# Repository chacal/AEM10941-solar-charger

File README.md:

# AEM10941 Solar Charger

KiCad hardware files for a simple [e-peas AEM10941](https://e-peas.com/product/aem10941/) based solar charger PCB.

## Schematics

* [PDF](AEM10941%20Solar%20Charger.pdf)

## Board rendering

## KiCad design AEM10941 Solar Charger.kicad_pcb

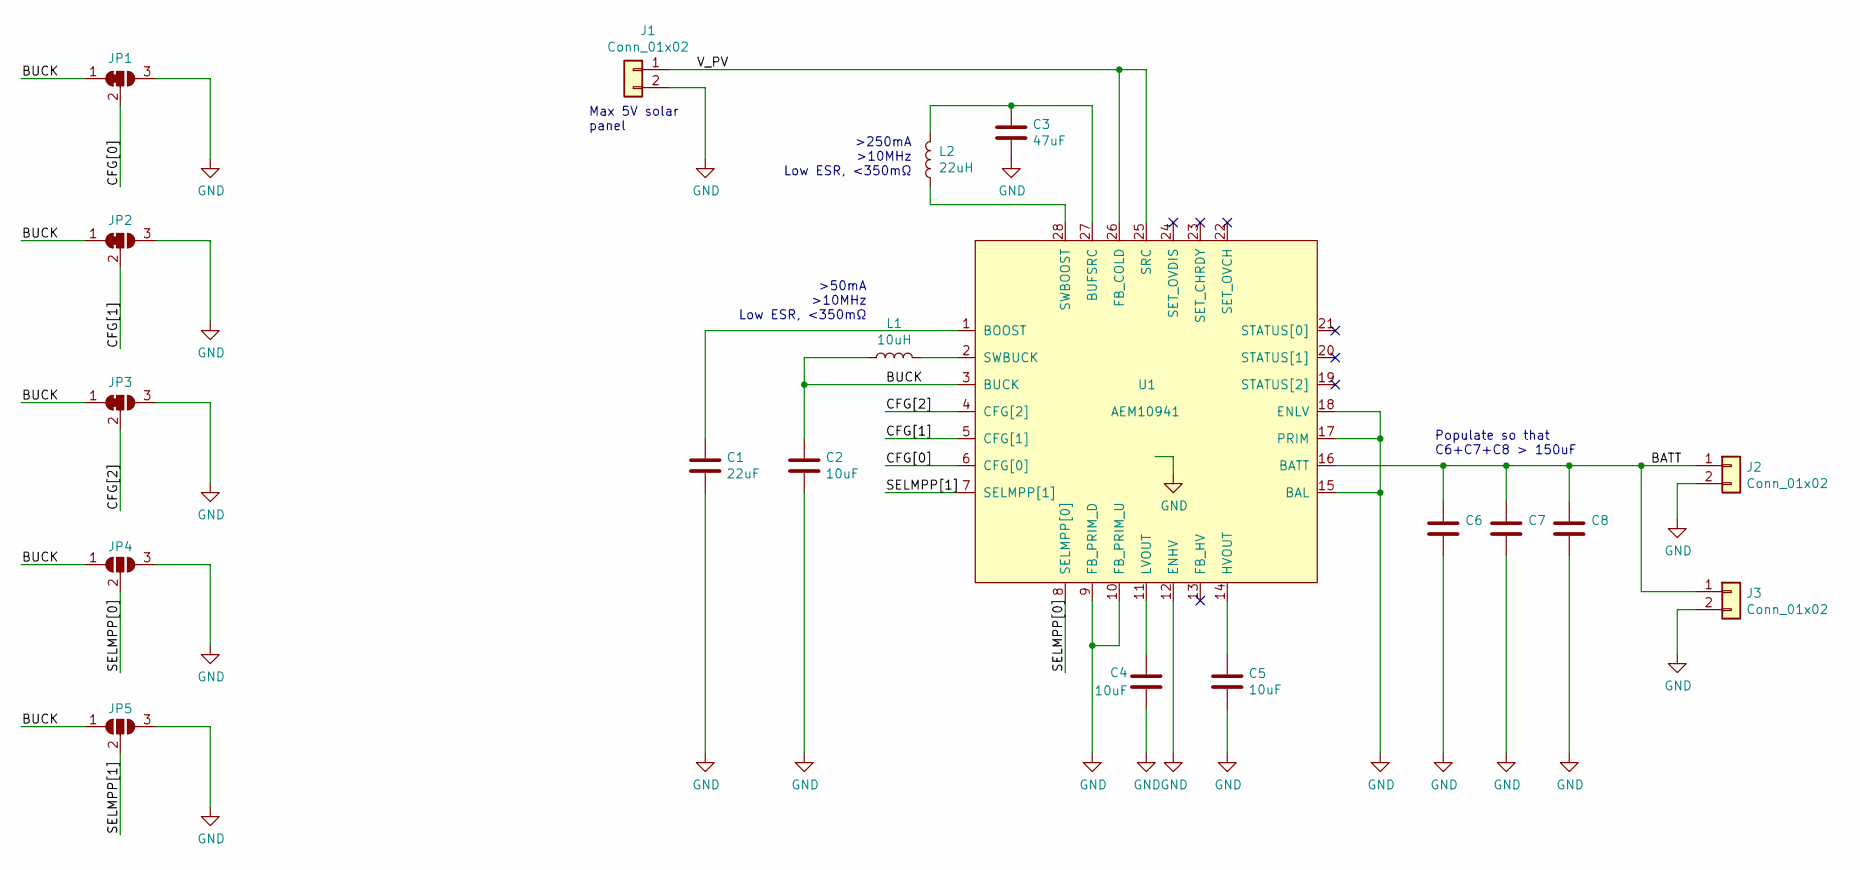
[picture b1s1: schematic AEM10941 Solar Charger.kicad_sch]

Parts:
C1: 22uF; C_0805_2012Metric
C2, C4, C5: 10uF; C_0805_2012Metric
C3: 47uF; C_0805_2012Metric
C6, C7, C8: 47uF; C_1206_3216Metric
J1, J2: Conn_01x02; JST_PH_S2B-PH-K_1x02_P2.00mm_Horizontal
J3: Conn_01x02; PinHeader_1x02_P2.54mm_Vertical
JP1, JP2, JP3: SolderJumper_3_Bridged12; SolderJumper-3_P1.3mm_Bridged12_RoundedPad1.0x1.5mm
JP4, JP5: SolderJumper_3_Open; SolderJumper-3_P1.3mm_Open_RoundedPad1.0x1.5mm
L1: 10uH; L_1210_3225Metric
L2: 22uH; L_Taiyo-Yuden_NR-40xx_HandSoldering
U1: AEM10941; QFN-28-1EP_5x5mm_P0.5mm_EP3.35x3.35mm_handsolder

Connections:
/BATT: C6.1, C7.1, C8.1, J2.1, J3.1, U1.16 (BATT)
/BUCK: C2.1, JP1.1 (A), JP2.1 (A), JP3.1 (A), JP4.1 (A), JP5.1 (A), L1.1, U1.3 (BUCK)
/CFG[0]: JP1.2 (C), U1.6 (CFG[0])
/CFG[1]: JP2.2 (C), U1.5 (CFG[1])
/CFG[2]: JP3.2 (C), U1.4 (CFG[2])
/SELMPP[0]: JP4.2 (C), U1.8 (SELMPP[0])
/SELMPP[1]: JP5.2 (C), U1.7 (SELMPP[1])
/V_PV: J1.1, U1.25 (SRC), U1.26 (FB_COLD)
GND: C1.2, C2.2, C3.2, C4.2, C5.2, C6.2, C7.2, C8.2, J1.2, J2.2, J3.2, JP1.3 (B), JP2.3 (B), JP3.3 (B), JP4.3 (B), JP5.3 (B), U1.9 (FB_PRIM_D), U1.10 (FB_PRIM_U), U1.12 (ENHV), U1.15 (BAL), U1.17 (PRIM), U1.18 (ENLV), U1.29 (GND)
unnamed: C1.1, U1.1 (BOOST)
unnamed: C3.1, L2.2, U1.27 (BUFSRC)
unnamed: C4.1, U1.11 (LVOUT)
unnamed: C5.1, U1.14 (HVOUT)
unnamed: L1.2, U1.2 (SWBUCK)
unnamed: L2.1, U1.28 (SWBOOST)

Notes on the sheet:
>50mA >10MHz Low ESR, <350mΩ
Populate so that C6+C7+C8 > 150uF
Max 5V solar panel
>250mA >10MHz Low ESR, <350mΩ

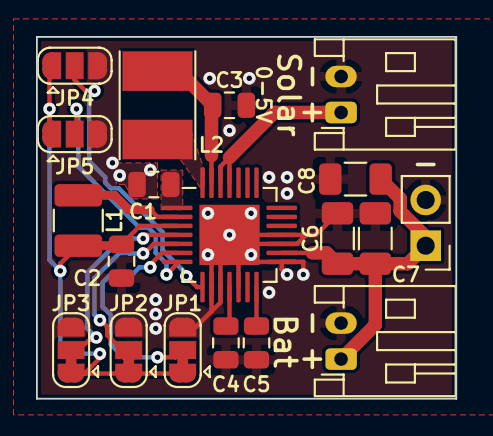
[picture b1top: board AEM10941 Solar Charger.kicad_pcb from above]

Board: 2 copper layers, 23.3 x 20.1 mm, 19 parts (0 on the bottom side), 15 nets.

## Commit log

2022-01-20 Create LICENSE
